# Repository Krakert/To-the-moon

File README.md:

# Stefan de Kraker IoT individual project
For this individual project I have chosen for the blueprint: "To the moon".
This blueprint focus on making a device that keeps an eye on your savings in the crypto market.
Therefore I'm making a small embedded devices that will show this.
On this Gitlab repo you will find everything you need to know to about the project.

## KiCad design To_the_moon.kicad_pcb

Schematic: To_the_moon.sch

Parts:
C1, C2: 14pf; C_0402_1005Metric; LCSC C458857
C3, C4, C8, C10: 10uf; C_0603_1608Metric; LCSC C19702
C5, C6: 100uf; C_1206_3216Metric; LCSC C15008
C7, C9: 0.1uf; C_0603_1608Metric; LCSC C14663
C11, C14: 4.7uf; C_1206_3216Metric; LCSC C29823
C12, C13: 1uf; C_0603_1608Metric; LCSC C15849
D1, D5: Blue; LED_0805_2012Metric; LCSC C2293
D3, D6: Yellow; LED_0805_2012Metric; LCSC C2296
D4: WS2812B; WS2812-2020; LCSC C965555
D7: D_Schottky; D_SOD-123; LCSC C8598
H1, H2, H3, H4: MountingHole; MountingHole_3.2mm_M3_DIN965_Pad
H6: MountingHole; MountingHole_2.1mm
IC1: DW01A; SOT-23-6; MPN DW01A; LCSC C351410
J1: USB_B_Micro; USB_Micro-B_Molex-105017-0001; LCSC C132563
J2: connector lipo; PinHeader_1x02_P2.00mm_Vertical
J3: Conn_01x09_Male; PinHeader_1x09_P2.00mm_Vertical
J4: Conn_01x03_Female; PinHeader_1x03_P2.00mm_Vertical_SMD_Pin1Left
L1: 10uh; L_1206_3216Metric; LCSC C1051
Q1: FS8205; SOT-23-6; PARTREV 1.9; LCSC C2830320
Q2, Q3: BC847; SOT-23; LCSC C181140
Q4: AO3401A; SOT-23; LCSC C15127
R1, R3, R5: 1.2K; R_0603_1608Metric; LCSC C22765
R2, R4, R8, R9, R14, R18: 10K; R_0603_1608Metric; LCSC C25804
R6: 1K; R_0603_1608Metric; LCSC C21190
R7, R10: 470; R_0603_1608Metric; LCSC C23179
R11: 100; R_0603_1608Metric; LCSC C22775
R12, R13: 2K; R_0603_1608Metric; LCSC C22975
R15: 100K; R_0603_1608Metric; LCSC C25803
R16: 62K; R_0603_1608Metric; LCSC C23221
R17: 8.2K; R_0603_1608Metric; LCSC C25981
SW1, SW2: SW_Push; TS-1187A-B-A-B; LCSC C318884
U1: ESP-12E; LCSC C82898
U2: TP4056; HSOP-8-1EP_3.9x4.9mm_P1.27mm_EP2.41x3.1mm; LCSC C16581
U3: CH340G; SOIC-16_3.9x9.9mm_P1.27mm; LCSC C14267
U4: MT3608; SOT-23-6; LCSC C84817
U5: AMS1117-3.3; SOT-223-3_TabPin2; LCSC C173386
Y1: 12MHz; Crystal_SMD_TXC_7M-4Pin_3.2x2.5mm; LCSC C93114

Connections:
5VUSB: D7.2, J1.1, Q4.1, R1.1, R3.1, R15.1, U2.4, U2.8
+3V3: C3.1, C4.1, C5.1, C6.1, C13.1, R2.2, R4.2, R12.2, R13.2, R14.2, R18.2, U1.8, U3.4, U3.16, U5.2
+5V: C14.1, J3.7, L1.2, R16.2, U4.1
/5V_: D4.4, J4.3
/D0: J3.6, U1.4
/D3: J3.1, Q3.3, R14.1, U1.18
/D5: J3.4, U1.5
/D6: J3.2, U1.6
/D7: J3.3, U1.7
/D8: J3.5, U1.16
/D+: J1.3, U3.5
/D-: J1.2, U3.6
/DTR: R8.2, U3.13
/EN: R2.1, U1.3
/GND_: D4.2, J4.2
/GPIO4: R18.1, SW2.1, U1.19
/LED: J3.9, U1.17
/LED_: D4.3, J4.1
/OC: IC1.3, Q1.6
/OD: IC1.1, Q1.4
/RST: C9.1, Q2.3, R4.1, SW1.1, U1.1
/RTS: R9.2, U3.14
/RX: D6.1, R7.1, U1.21
/TX: D5.1, R10.1, U1.22
/XI: C1.1, U3.7, Y1.1
/XO: C2.1, U3.8, Y1.3
GND: C1.2, C2.2, C3.2, C4.2, C5.2, C6.2, C8.2, C9.2, C10.2, C11.2, C12.2, C13.2, C14.2, J1.5, J1.6, J3.8, Q1.1, R5.2, R6.1, R15.2, R17.1, SW1.2, SW2.2, U1.15, U2.1, U2.3, U2.9, U3.1, U4.2, U5.1, Y1.2, Y1.4
unnamed: C7.1, IC1.5, R11.1
unnamed: C7.2, IC1.6, J2.2, Q1.3
unnamed: C8.1, J2.1, Q4.3, R11.2, U2.5
unnamed: D1.1, U2.6
unnamed: D1.2, R1.2
unnamed: D3.1, U2.7
unnamed: D3.2, R3.2
unnamed: D5.2, R12.1
unnamed: D6.2, R13.1
unnamed: IC1.2, R6.2
unnamed: Q1.2, Q1.5
unnamed: Q2.1, Q3.2, R8.1
unnamed: Q2.2, Q3.1, R9.1
unnamed: R5.1, U2.2
unnamed: R7.2, U3.2
unnamed: R10.2, U3.3
unnamed: R16.1, R17.2, U4.3
VCC: C10.1, C11.1, C12.1, D7.1, L1.1, Q4.2, U4.4, U4.5, U5.3

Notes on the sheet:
(14pfx14pf) / (14pf+14pf) + 5 = 12pf

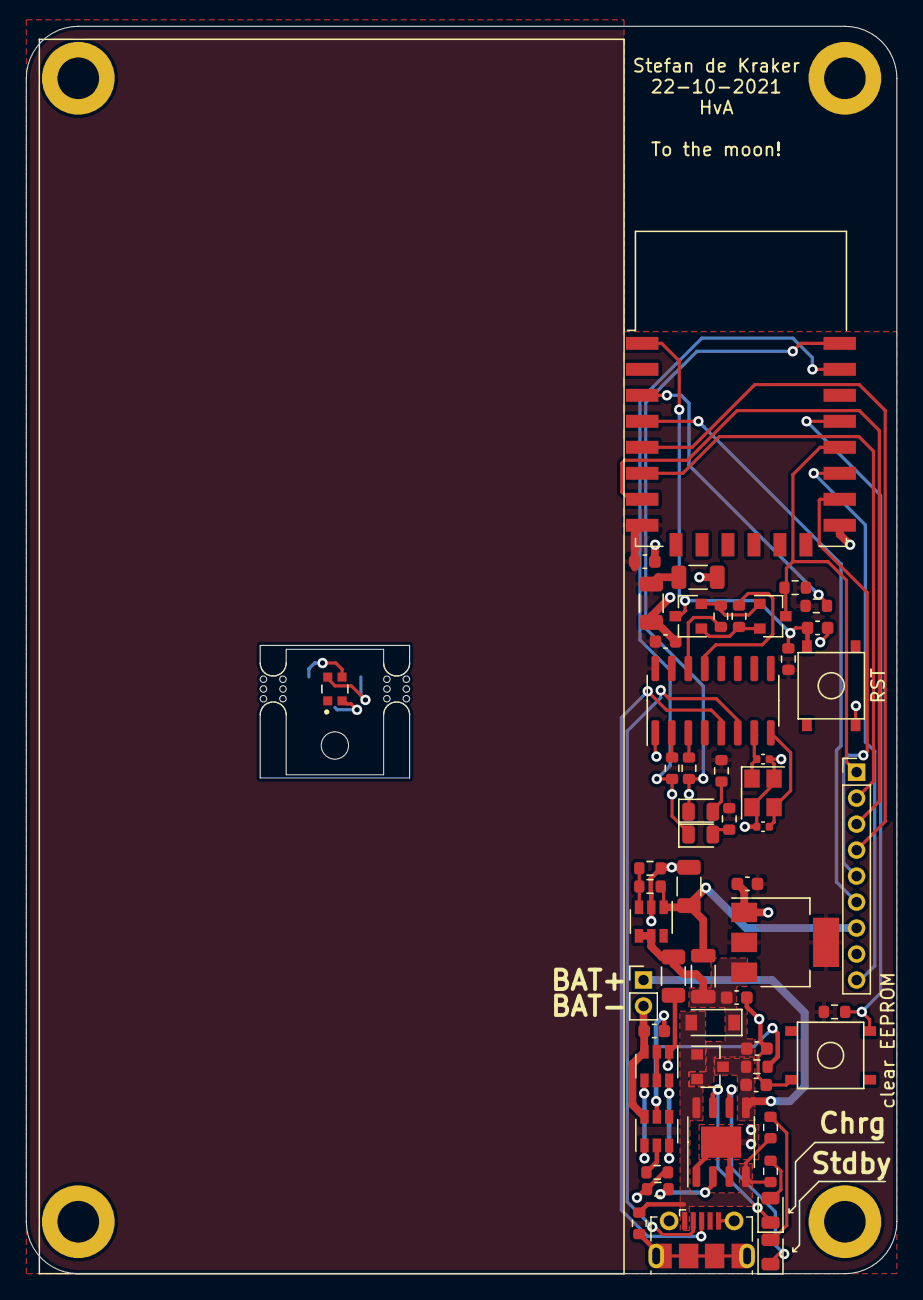
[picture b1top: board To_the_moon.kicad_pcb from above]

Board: 2 copper layers, 67.0 x 96.0 mm, 63 parts (1 on the bottom side), 45 nets.

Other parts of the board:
mouse-bite-2mm-slot, mouse-bite-2mm-slot#2: VAL**; mouse-bite-2mm-slot

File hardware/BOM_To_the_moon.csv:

Comment,Designator,Footprint,LCSC
"14pf","C1,C2","Capacitor_SMD:C_0402_1005Metric","C458857"
"4.7uf","C11,C14","Capacitor_SMD:C_1206_3216Metric","C29823"
"1uf","C12,C13","Capacitor_SMD:C_0603_1608Metric","C15849"
"10uf","C3,C4,C8,C10","Capacitor_SMD:C_0603_1608Metric","C19702"
"100uf","C5,C6","Capacitor_SMD:C_1206_3216Metric","C15008"
"0.1uf","C7,C9","Capacitor_SMD:C_0603_1608Metric","C14663"
"WS2812B","D4","LED_SMD:WS2812-2020","C965555"
"Blue","D1,D5","LED_SMD:LED_0805_2012Metric","C2293"
"Yellow","D3,D6","LED_SMD:LED_0805_2012Metric","C2296"
"D_Schottky","D7","Diode_SMD:D_SOD-123","C8598"
"MountingHole","H1,H2,H3,H4","MountingHole:MountingHole_3.2mm_M3_DIN965_Pad",""
"MountingHole","H6","MountingHole:MountingHole_2.1mm",""
"DW01A","IC1","Package_TO_SOT_SMD:SOT-23-6","C351410"
"USB_B_Micro","J1","Connector_USB:USB_Micro-B_Molex-105017-0001","C132563"
"connector lipo","J2","Connector_PinHeader_2.00mm:PinHeader_1x02_P2.00mm_Vertical",""
"Conn_01x09_Male","J3","Connector_PinHeader_2.00mm:PinHeader_1x09_P2.00mm_Vertical",""
"Conn_01x03_Female","J4","Connector_PinHeader_2.00mm:PinHeader_1x03_P2.00mm_Vertical_SMD_Pin1Left",""
"10uh","L1","Inductor_SMD:L_1206_3216Metric","C1051"
"FS8205","Q1","Package_TO_SOT_SMD:SOT-23-6","C2830320"
"BC847","Q2,Q3","Package_TO_SOT_SMD:SOT-23","C181140"
"AO3401A","Q4","Package_TO_SOT_SMD:SOT-23","C15127"
"470","R7,R10","Resistor_SMD:R_0603_1608Metric","C23179"
"100","R11","Resistor_SMD:R_0603_1608Metric","C22775"
"2K","R12,R13","Resistor_SMD:R_0603_1608Metric","C22975"
"100K","R15","Resistor_SMD:R_0603_1608Metric","C25803"
"62K","R16","Resistor_SMD:R_0603_1608Metric","C23221"
"8.2K","R17","Resistor_SMD:R_0603_1608Metric","C25981"
"10K","R2,R4,R8,R9,R14,R18","Resistor_SMD:R_0603_1608Metric","C25804"
"1.2K","R1,R3,R5","Resistor_SMD:R_0603_1608Metric","C22765"
"1K","R6","Resistor_SMD:R_0603_1608Metric","C21190"
"SW_Push","SW1,SW2","Button_Switch_SMD:TS-1187A-B-A-B","C318884"
"ESP-12E","U1","RF_Module:ESP-12E","C82898"
"TP4056","U2","Package_SO:HSOP-8-1EP_3.9x4.9mm_P1.27mm_EP2.41x3.1mm","C16581"
"CH340G","U3","Package_SO:SOIC-16_3.9x9.9mm_P1.27mm","C14267"
"MT3608","U4","Package_TO_SOT_SMD:SOT-23-6","C84817"
"AMS1117-3.3","U5","Package_TO_SOT_SMD:SOT-223-3_TabPin2","C173386"
"12MHz","Y1","Crystal:Crystal_SMD_TXC_7M-4Pin_3.2x2.5mm","C93114"

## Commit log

2021-09-15 Init Hardware design
2021-09-15 Fixed colours in hardware overview
2021-09-23 Start AP to Station functions
2021-09-23 Documentation can be found in the WIKI
2021-09-24 commit files of the STM32 UART to ESP programm
2021-09-24 Add new file
2021-09-26 Made functions that enable the use of the EEPROM, can read and write to the EEPROM, also checks the data and can dumb the data in raw (ascii) or char to the user, close #7
2021-09-26 ini file to compile with Platform.io
2021-09-26 Added function to extract parameter from the 2D array return by the function getConfigFromEeprom, and some cleanup at the For loops
2021-09-26 Added HTML code for the softAP to return on connect
2021-09-26 Remove the EEPROM code to own files (eeprom_handler.cpp & eeprom_handler.h)
2021-09-26 Code is in a state where when no SSID and PSW are present in the EEPROM, setup a softAP, here you can input your wifi's SSID and PSW. Those are then saved to the EEPROM, On powercycle, the data is lo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
2021-09-28 Init LCD files
2021-09-28 Init Tech an User doc, need to be added to Main/README.md
2021-09-28 grammer correct
2021-09-28 Init Hardware schematic
2021-09-28 Cleanup branch
2021-09-28 added files
2021-09-29 Cleanup
2021-09-30 Init display handler file
2021-10-04 Fixed mistake in de Doc in the file, added missing parameters
2021-10-04 Init file for handeling the LCD screen
2021-10-04 Changed #define to const static, this makes some parameters easier to use in other functions and or file.
2021-10-05 Added boot progress bar and setup screen AP
2021-10-05 Added boot function and X & Y center values
2021-10-05 Simple program to show Boot and Init screen AP
2021-10-05 Fixed typo
2021-10-05 rollback main
2021-10-05 Rollback platformio
2021-10-11 Rename eeprom files
2021-10-11 Cleanup main.cpp
2021-10-11 Added JSON lib
2021-10-11 Simple cleanup
2021-10-11 Init HTTP GET and POST files
2021-10-11 Init server side for DB calls via HTTP GET
2021-10-12 Init HTML files for webserver, not running it on the ESP
2021-10-12 Cleanup main
2021-10-21 renamed wifi cpp and h files
2021-10-21 added littleFS
2021-10-21 moved files into the Folder data, used for littleFS
2021-10-21 renamed for wifiHandler.h
2021-10-21 small changes
2021-10-22 Library for the pcb design
2021-10-22 Production files
2021-10-22 Added kicad main files
2021-10-22 Update PDF schematic
2021-10-25 added JS to make the calls to the DB
2021-10-25 added css
2021-10-25 Added calls to handle and added CROS support
2021-10-30 resolved #10, added HTTP GET call to database
2021-10-30 close #10, fixed server side for HTTP GET calls from ESP
2021-10-31 Fixed bug where password is saved twice in EEPROM
2021-10-31 Added function to ask/save/update coin list from db, close#11
2021-10-31 close #11
2021-11-01 Added PCB in STEP format
2021-11-10 added upload speed, uploads much faster to esp
2021-11-10 added constuctor and function to get 8 data points from DB
2021-11-10 added get/<coinId> to work with functions in requestHandler
2021-11-10 added touch support, and plot graph, close #9
2021-11-10 small tweaks in getting a coin Id from the 2D array
2021-11-10 added full GUI and touch support, close #5 #6
2021-11-11 Changed color setup screen and speed boot screen
2021-11-11 Lowered API call delay from 50 to 25ms
2021-11-11 Added clear EEPROM via button, close #12
2021-11-11 Raised delay from 90 to 120ms
2021-11-11 Added code, percentage growth
2021-11-11 Added the ability to define the amount of data points in the graph
2021-11-11 fixed #13 with a bit of debouncing code
2021-11-11 deleted Serial.print
2021-11-11 fault in procent view
2021-11-11 Fixed webserver on ESP, resloved #14
2021-11-12 Removed unused function
2021-11-12 Updated schematic
2021-11-12 move files to folder
2021-11-12 Closed #15, show IP on startup for 3s
2021-11-12 Clear display before drawing new data
2021-11-12 Added user manual V1
2021-11-12 small offset fix in the html
2021-11-12 Added UI explanation
2021-11-13 Update .gitlab-ci.yml file
2021-11-13 fix in Doc
2021-11-14 Fixed problem drawing over the setup screen when no AP
2021-11-14 Fixed problem with the procent diff
